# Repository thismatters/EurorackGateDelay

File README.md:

# Gate Delay

The circuit here is based on the [Yusynth Gate Delay](https://yusynth.net/Modular/EN/GATEDELAY/index.html) with minor tweaks to make it more Eurorack friendly. The changes I've made are thus:
* Selected resistors appropriate for +/-12V rails,
* Added polarity protection so that a backward power header doesn't fry anything (twin series schotty diodes: BAT54SL),
* Full surface mount design,
* Preseve gate duration in the delay.

The maximum delay is approximately 250ms, although by changing some resistor or capacitor values you may be able to extend that by quite a degree. I kept the delay to a moderate value to prevent distortion in delay duration. The main enhancement here over the original circuit is that the duration of the output gate mimicks the duration of the input gate. The output duration can be slightly longer than the input when the delay is set to high values.

The Yusynth page is a treasure trove of information about this circuit that I am too amateur to claim as my own; please read that outstanding page before using this circuit. The page provides many details and other implementations of this circuit that you may find suitable.

The KiCAD project here uses the library/footprints [found in my companion repo](https://github.com/thismatters/EurorackKiCAD).

## Width

12hp on an Intellijel 1U rack.

## Inputs

Jack for Gate

Potentiometer for delay duration

## Outputs

LED to indicate gate output

Jacks:
- Gate
- Slew (Logarithmic)

## Vendors

There are part numbers in the [BOM](gate-delay.csv) for many of the parts (not for basic passives though) at the following vendors:

* [Mouser](https://www.mouser.com): Needs no introduction. Get your ICs from here (or [digikey](https://www.digikey.com)).
* [Tayda Electronics](https://www.taydaelectronics.com/): Good supplier for passive components; audio jacks, and potentiometers. Their audio jacks are slightly smaller than the thonkiconn from thonk.
* [Love My Switches](https://lovemyswitches.com/): Has [really good knobs](https://lovemyswitches.com/anodized-aluminum-knob-the-lo-fi-1-4-smooth-shaft-12-5mm-od/) to go on those potentiometers!
* [OSHPark](https://oshpark.com/): Fast and (relatively) cheap PCB manufacturer. Prototype run pending.

## Changelog

### V1

* Updated resistor value for R8 to 22K

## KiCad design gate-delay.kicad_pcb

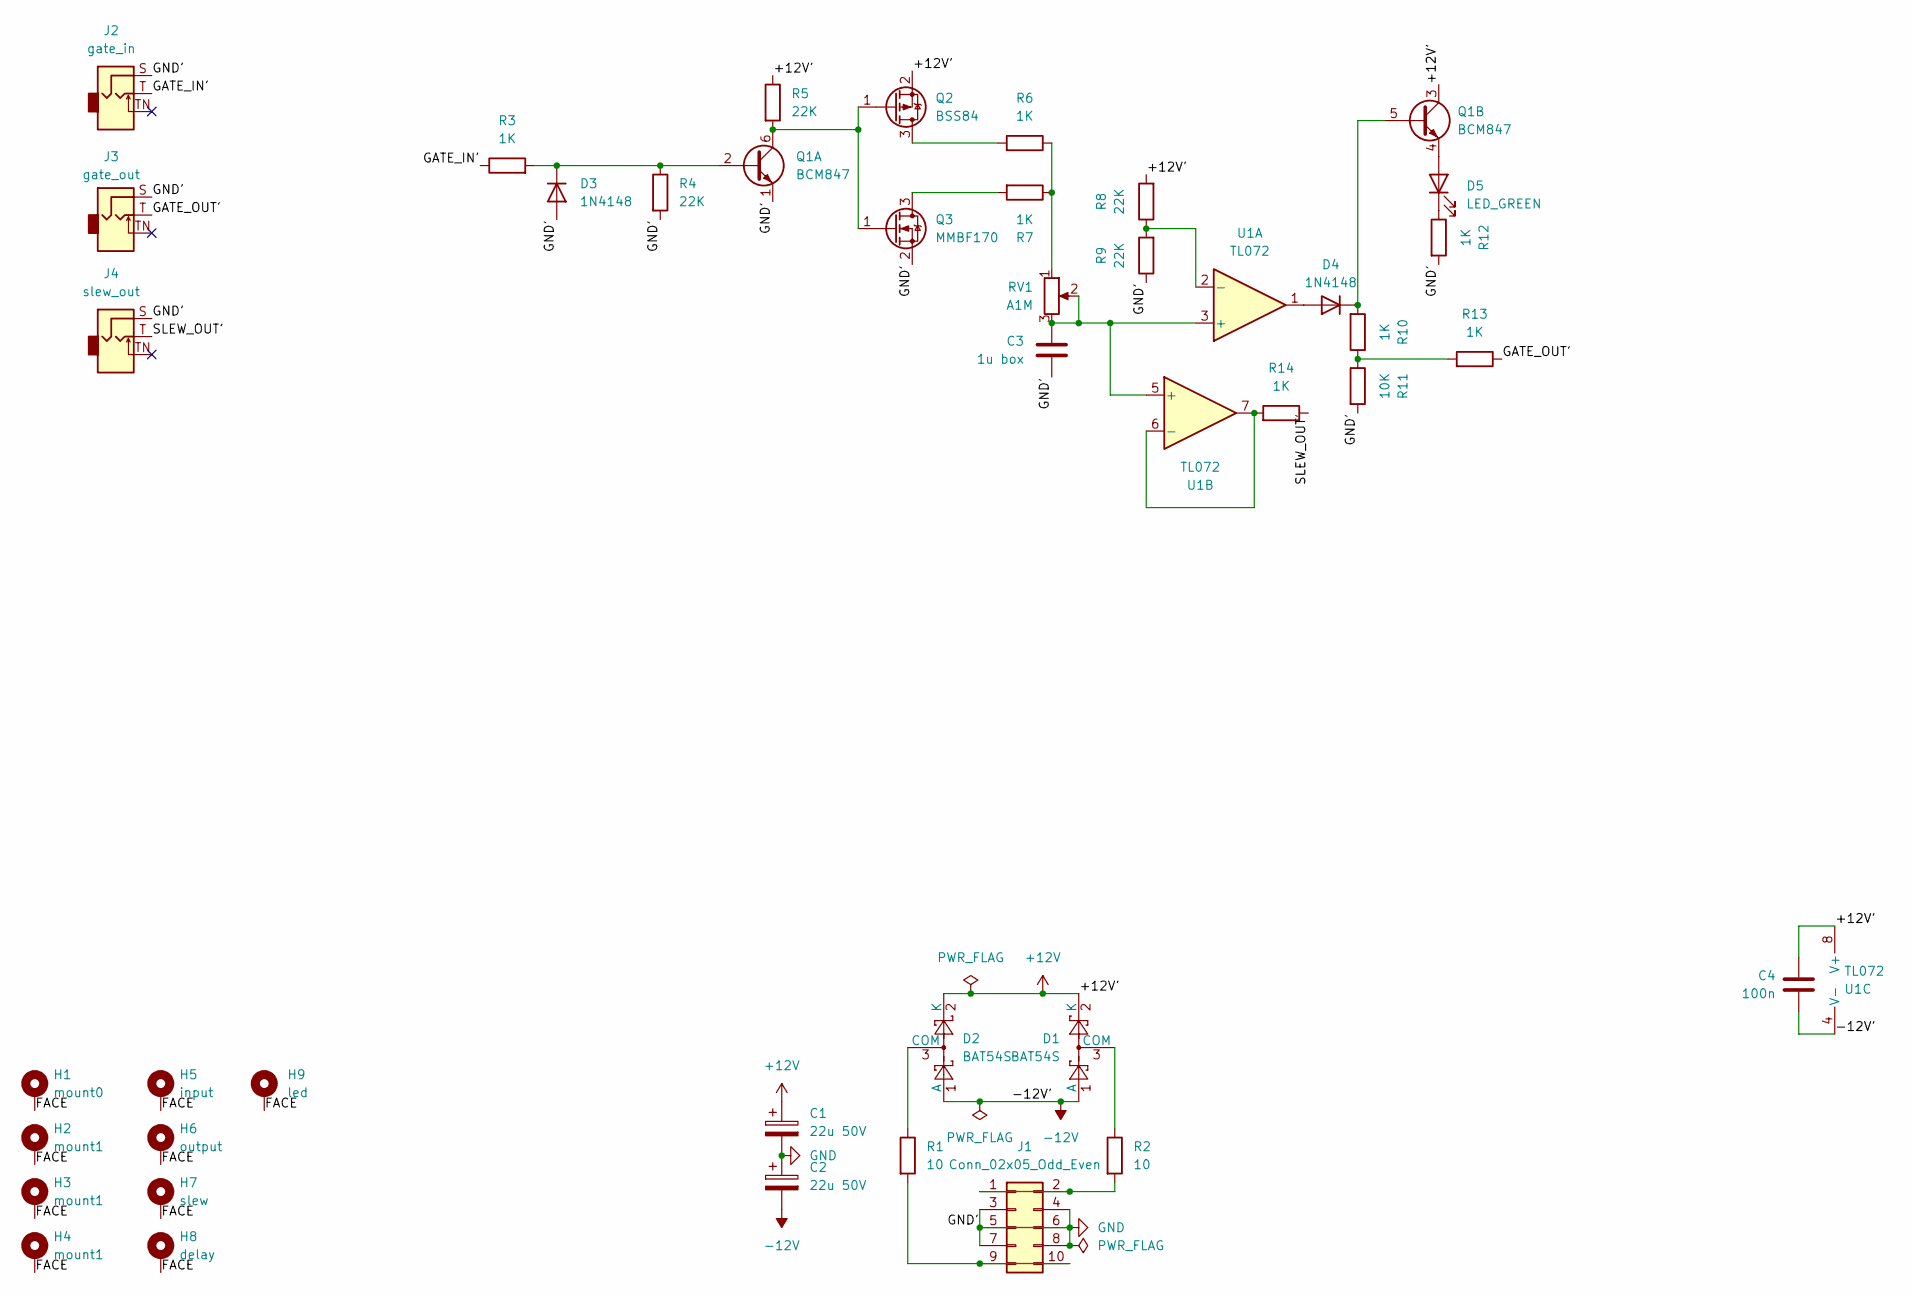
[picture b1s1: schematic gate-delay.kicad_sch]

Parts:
C1, C2: 22u 50V; CP_Radial_D5.0mm_P2.50mm
C3: 1u box; C_Rect_L7.2mm_W5.5mm_P5.00mm_FKS2_FKP2_MKS2_MKP2
C4: 100n; C_0805_2012Metric
D1, D2: BAT54S; SOT-23; PartNum 863-BAT54SLT1G
D3, D4: 1N4148; D_SOD-323_HandSoldering
D5: LED_GREEN; LED_D3.0mm
H1: mount0; Mech-MountingHole
H2, H3, H4: mount1; Mech-MountingHole
H5: input; Mech-AudioJack-Hole-Input-Gate
H6: output; Mech-AudioJack-Hole-Output-Gate
H7: slew; Mech-AudioJack-Hole-Output-CV
H8: delay; Mech-Potentiometer-Hole_level_90deg
H9: led; Mech-LED-Hole-3mm-Bezel
J1: Conn_02x05_Odd_Even; PinHeader_2x05_P2.54mm_Vertical; PartNum A-2939
J2: gate_in; AudioJack2_Tayda_A-2566; PartNum A-2566
J3: gate_out; AudioJack2_Tayda_A-2566; PartNum A-2566
J4: slew_out; AudioJack2_Tayda_A-2566; PartNum A-2566
Q1: BCM847; TSOP-6_1.65x3.05mm_P0.95mm; PartNum 771-BCM847DS135
Q2: BSS84; SOT-23; PartNum 512-BSS84
Q3: MMBF170; SOT-23; PartNum 863-MMBF170LT1G
R1, R2: 10; R_0805_2012Metric
R3, R6, R7, R10, R12, R13, R14: 1K; R_0805_2012Metric
R4, R5, R8, R9: 22K; R_0805_2012Metric
R11: 10K; R_0805_2012Metric
RV1: A1M; Potentiometer_RV16AF-41-15R1
U1: TL072; SOIC-8_3.9x4.9mm_P1.27mm; PartNum 771-BCM847DS135

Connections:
+12V: C1.1, C4.1, D1.2 (K), D2.2 (K), Q1.3 (C2), Q2.2 (S), R5.1, R8.2, U1.8 (V+)
-12V: C2.2, C4.2, D1.1 (A), D2.1 (A), U1.4 (V-)
/FACE: H1.1, H2.1, H3.1, H4.1, H5.1, H6.1, H7.1, H8.1, H9.1
/GATE_IN': J2.T, R3.1
/GATE_OUT': J3.T, R13.1
/SLEW_OUT': J4.T, R14.1
GND: C1.2, C2.1, C3.2, D3.2 (A), J1.3, J1.4, J1.5, J1.6, J1.7, J1.8, J2.S, J3.S, J4.S, Q1.1 (E1), Q3.2 (S), R4.2, R9.1, R11.2, R12.2
unnamed: D1.3 (COM), R2.1
unnamed: D2.3 (COM), R1.1
unnamed: D3.1 (K), Q1.2 (B1), R3.2, R4.1
unnamed: D4.2 (A), U1.1
unnamed: D4.1 (K), Q1.5 (B2), R10.2
unnamed: D5.2 (A), Q1.4 (E2)
unnamed: D5.1 (K), R12.1
unnamed: J1.1, J1.2, R2.2
unnamed: J1.9, J1.10, R1.2
unnamed: Q1.6 (C1), Q2.1 (G), Q3.1 (G), R5.2
unnamed: Q2.3 (D), R6.2
unnamed: Q3.3 (D), R7.2
unnamed: R6.1, R7.1, RV1.1
unnamed: R10.1, R11.1, R13.2
unnamed: C3.1, RV1.2, RV1.3, U1.3 (+), U1.5 (+)
unnamed: R8.1, R9.2, U1.2 (-)
unnamed: R14.2, U1.6 (-), U1.7

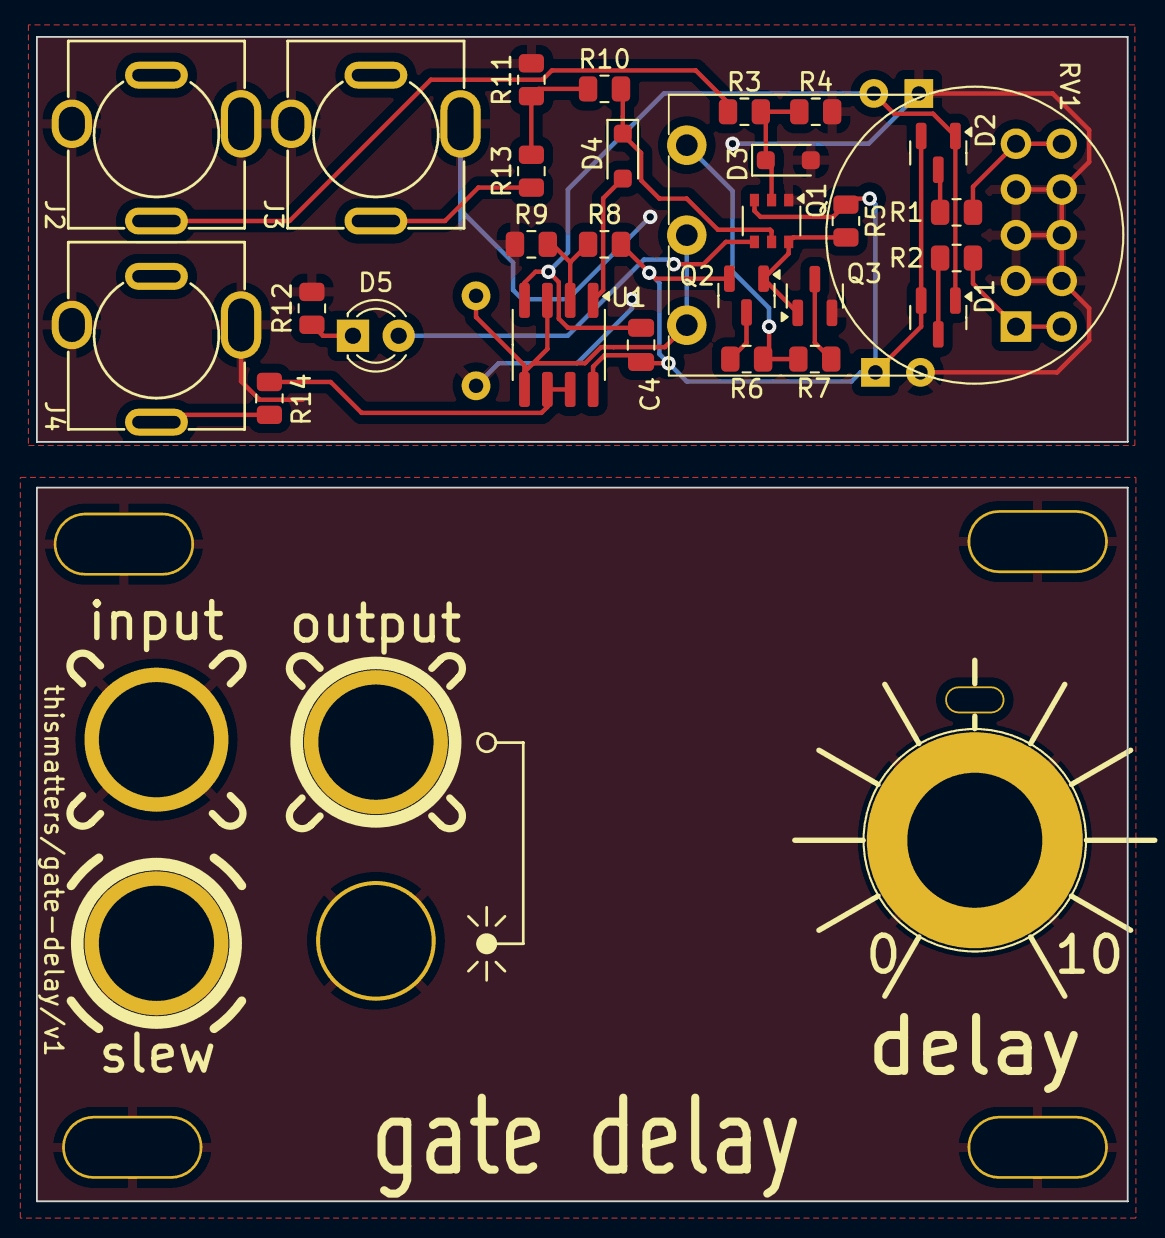
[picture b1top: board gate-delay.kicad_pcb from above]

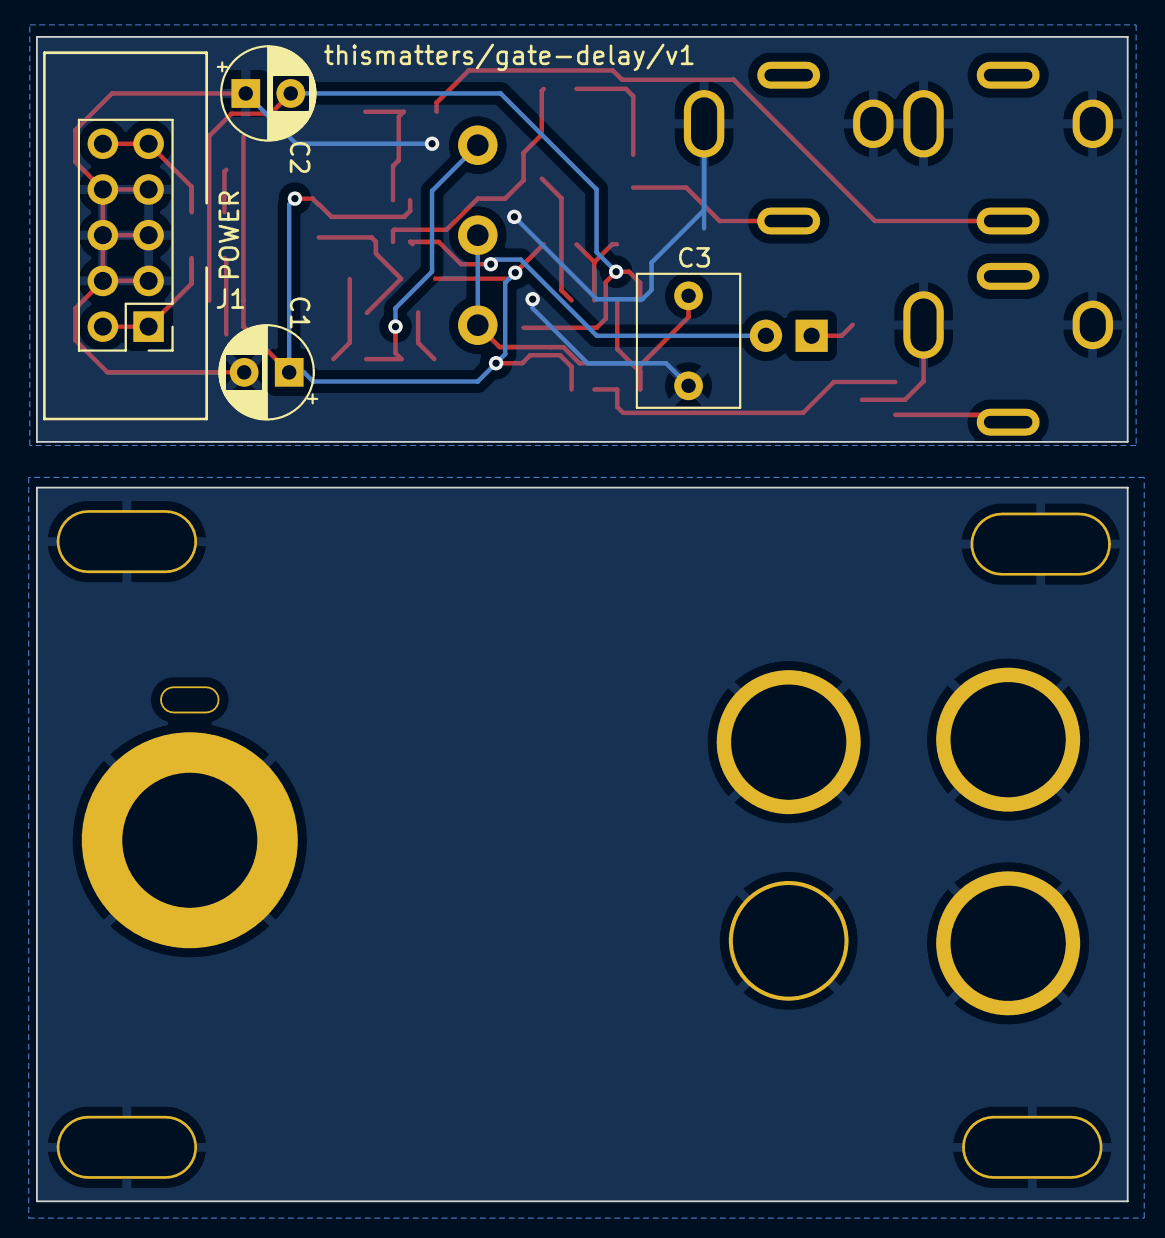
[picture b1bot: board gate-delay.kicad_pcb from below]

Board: 2 copper layers, 60.6 x 64.7 mm, 41 parts (4 on the bottom side), 24 nets.

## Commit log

2025-01-05 fix: try to maintain gate duration
2025-04-05 feat: v0 pcb layed out
2026-01-17 v1 ready (uses the v0 board)
